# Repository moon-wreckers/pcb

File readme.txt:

Team I - MRSD'18
				Power Distribution Board
					   6 Nov 2017

Summary:
	
	The necessary features for the power distribtion board are to power the camera (12V, 0.42A), motor drivers 2x(12V, 15-20A), steering motors 2x(12V, 0.42A), the HTC VIVE beacon (12V, 0.40A), winch mechanism(5V, 0.90A), on-board computer(5V, 3A), GPS(5V, 0.08A) and inertial measurement unit (5V, 0.05A).
	
Maximum 12v Current: 42.06A
Maximum Theoretical Current: 45.19A
Total Nominal Current: 4.09A

Discussion:
	The on-board power supply is from a set of 12V batteries. Considering that majority of the on-board components have to powered using 12V supply - we have designed a 12V power distribution board, that further reduces to 5V wherever necessary. In order to have a bank of the 5V power supply pins, we have an off the shelf 12V-5V power regulator, that has been supplied with the on-board computer, as the power source to the extendable 5V power bank. 

	Further, in order to limit the power (current) drawn by various components the supply has been branched to shield components that have current limit less than or equal to 3A, 6.25A and 25A (15 + 6.25 +3 A).
	
	For example, the 12V to 5V regulator will be powered by the [12V, 3A] branch. Thus, protecting the components from (sudden, uncpredicted) excessive power requirements owing to unknown external conditions.

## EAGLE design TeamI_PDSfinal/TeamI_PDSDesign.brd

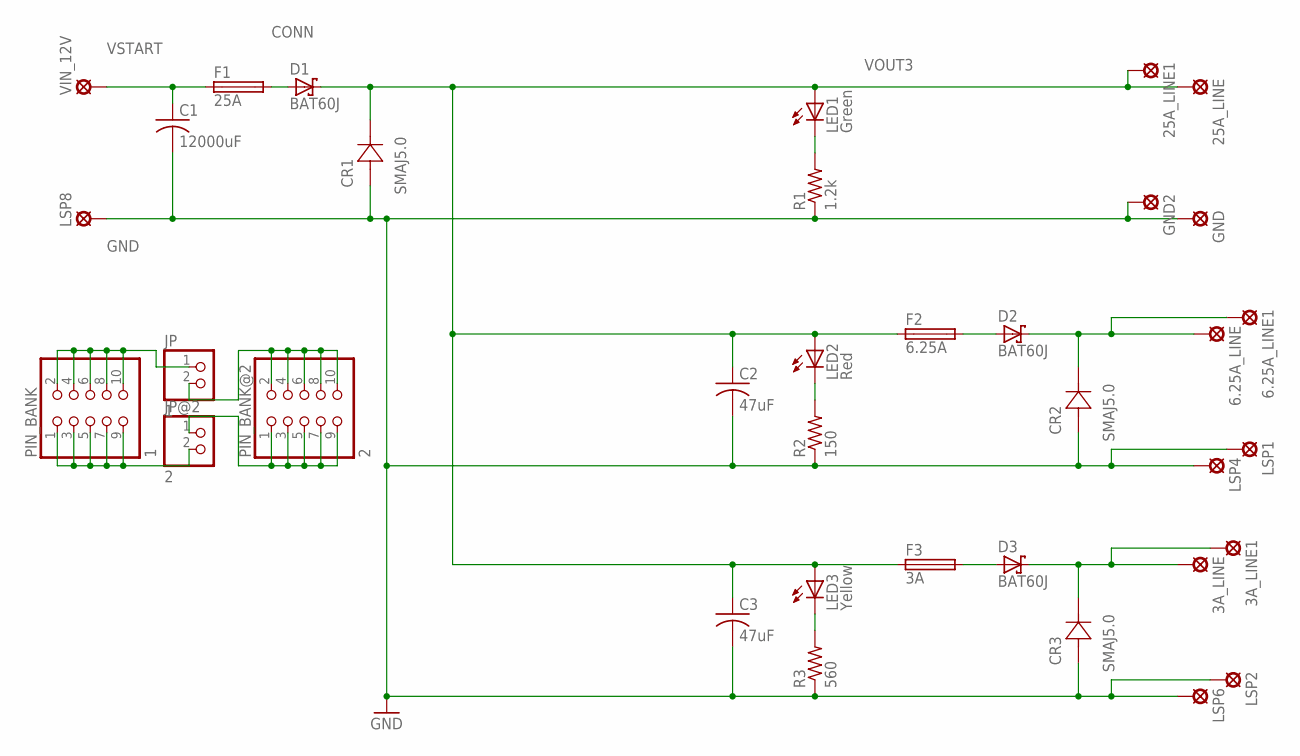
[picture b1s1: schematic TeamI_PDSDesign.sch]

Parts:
3A_LINE, 3A_LINE1, 6.25A_LINE, 6.25A_LINE1, 25A_LINE, 25A_LINE1: SE13
C1: 12000uF; C1206K
C2, C3: 47uF; C1206K
CR1, CR2, CR3: SMAJ5.0; SMASERIES
D1, D2, D3: BAT60J; SOD323_ST
F1: 25A; TE5
F2: 6.25A; TE5
F3: 3A; TE5
GND, GND2: SE13
JP: 1; 1X02
JP@2: 2; 1X02
LED1: Green; CHIPLED_1206
LED2: Red; CHIPLED_1206
LED3: Yellow; CHIPLED_1206
LSP1, LSP2, LSP4, LSP6, LSP8: SE13
PIN_BANK: 1; 2X05
PIN_BANK@2: 2; 2X05
R1: 1.2k; R1206
R2: 150; R1206
R3: 560; R1206
VIN_12V: SE13

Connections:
CONN: D1.A, F1.2
GND: C1.2, C2.2, C3.2, CR1.2 (1), CR2.2 (1), CR3.2 (1), GND.MP, GND2.MP, LSP1.MP, LSP2.MP, LSP4.MP, LSP6.MP, LSP8.MP, R1.1, R2.1, R3.1
unnamed: JP@2.1, PIN_BANK@2.1, PIN_BANK@2.3, PIN_BANK@2.5, PIN_BANK@2.7, PIN_BANK@2.9
unnamed: JP@2.2, PIN_BANK.1, PIN_BANK.3, PIN_BANK.5, PIN_BANK.7, PIN_BANK.9
unnamed: LED1.C, R1.2
unnamed: JP.1, PIN_BANK.2, PIN_BANK.4, PIN_BANK.6, PIN_BANK.8, PIN_BANK.10
unnamed: JP.2, PIN_BANK@2.2, PIN_BANK@2.4, PIN_BANK@2.6, PIN_BANK@2.8, PIN_BANK@2.10
unnamed: D2.A, F2.2
unnamed: 6.25A_LINE.MP, 6.25A_LINE1.MP, CR2.1 (2), D2.C
unnamed: LED2.C, R2.2
unnamed: D3.A, F3.2
unnamed: 3A_LINE.MP, 3A_LINE1.MP, CR3.1 (2), D3.C
unnamed: LED3.C, R3.2
VOUT3: 25A_LINE.MP, 25A_LINE1.MP, C2.1, C3.1, CR1.1 (2), D1.C, F2.1, F3.1, LED1.A, LED2.A, LED3.A
VSTART: C1.1, F1.1, VIN_12V.MP

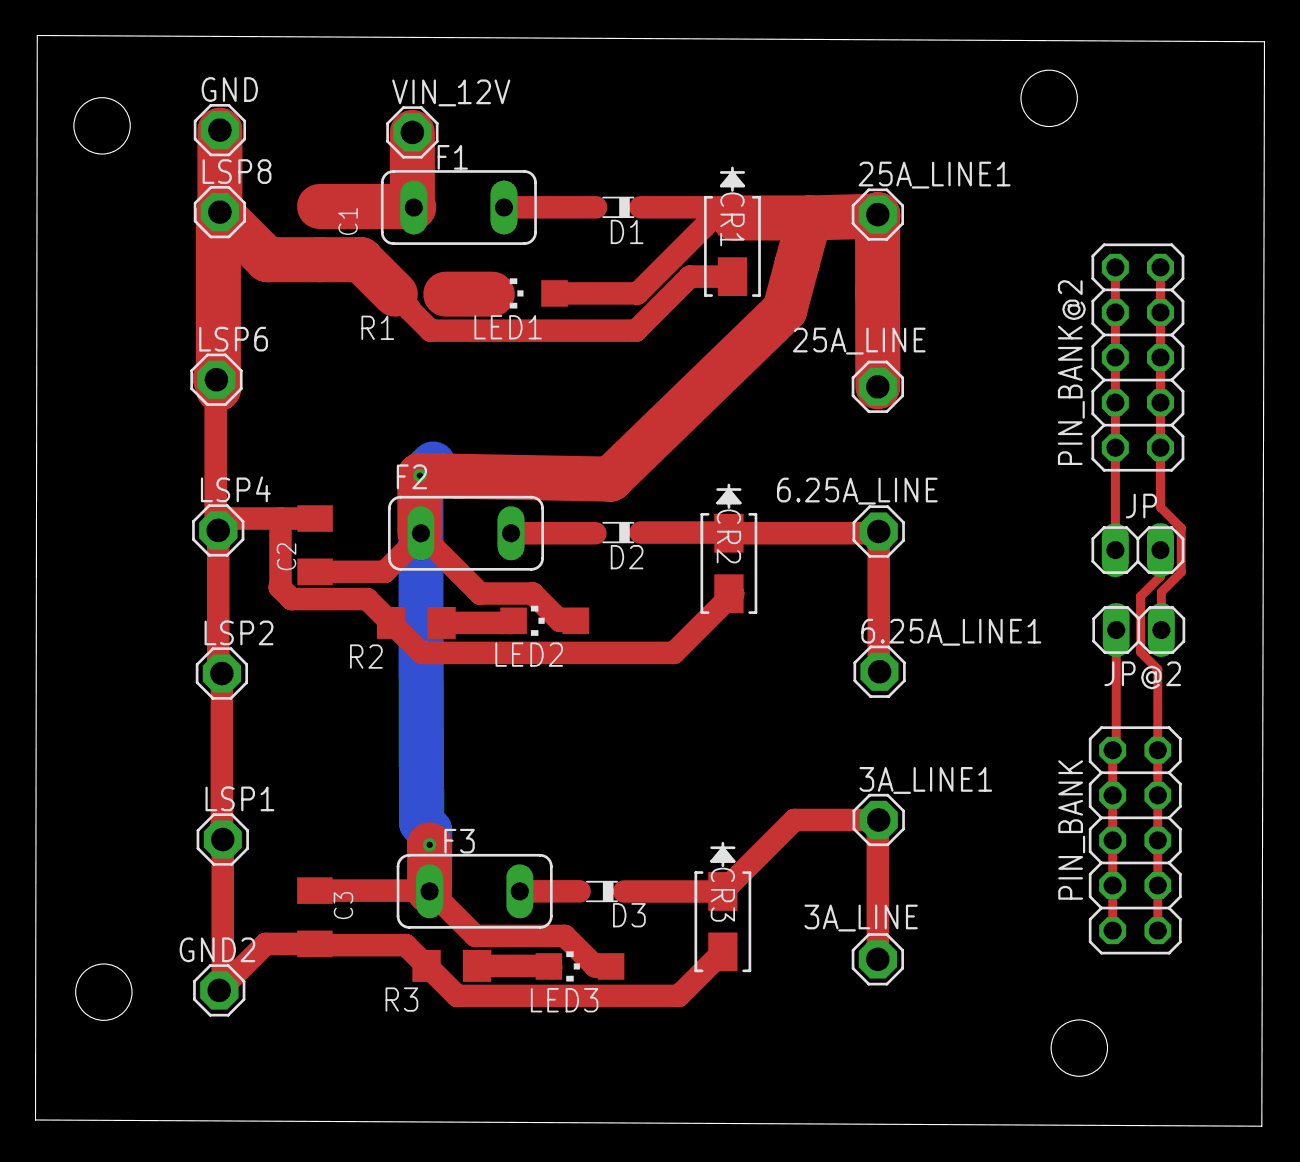
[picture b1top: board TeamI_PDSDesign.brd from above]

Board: 2 copper layers, 69.2 x 61.4 mm, 36 parts (0 on the bottom side), 15 nets.

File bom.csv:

"Part";"Value";"Device";"Package";"Description";"MANUFACTURER_PART_NUMBER";"MF";"MPN";"OC_FARNELL";"OC_NEWARK";"VENDOR";
"3A_LINE";"SE13";"SE13";"SE13";"SOLDER PAD E1542,  drill 1,3mm, distributor Buerklin, 07F815";"";"";"";"";"";"";
"3A_LINE1";"SE13";"SE13";"SE13";"SOLDER PAD E1542,  drill 1,3mm, distributor Buerklin, 07F815";"";"";"";"";"";"";
"6.25A_LINE";"SE13";"SE13";"SE13";"SOLDER PAD E1542,  drill 1,3mm, distributor Buerklin, 07F815";"";"";"";"";"";"";
"6.25A_LINE1";"SE13";"SE13";"SE13";"SOLDER PAD E1542,  drill 1,3mm, distributor Buerklin, 07F815";"";"";"";"";"";"";
"25A_LINE";"SE13";"SE13";"SE13";"SOLDER PAD E1542,  drill 1,3mm, distributor Buerklin, 07F815";"";"";"";"";"";"";
"25A_LINE1";"SE13";"SE13";"SE13";"SOLDER PAD E1542,  drill 1,3mm, distributor Buerklin, 07F815";"";"";"";"";"";"";
"C1";"12000uF";"C-USC1206K";"C1206K";"CAPACITOR, American symbol";"";"";"";"";"";"";
"C2";"47uF";"C-USC1206K";"C1206K";"CAPACITOR, American symbol";"";"";"";"";"";"";
"C3";"47uF";"C-USC1206K";"C1206K";"CAPACITOR, American symbol";"";"";"";"";"";"";
"CR1";"SMAJ5.0";"SMAJ5.0";"SMASERIES";"";"SMAJ5.0";"";"";"";"";"Littelfuse Inc";
"CR2";"SMAJ5.0";"SMAJ5.0";"SMASERIES";"";"SMAJ5.0";"";"";"";"";"Littelfuse Inc";
"CR3";"SMAJ5.0";"SMAJ5.0";"SMASERIES";"";"SMAJ5.0";"";"";"";"";"Littelfuse Inc";
"D1";"BAT60J";"BAT60J";"SOD323_ST";"Schottky barrier diode";"";"";"";"";"";"";
"D2";"BAT60J";"BAT60J";"SOD323_ST";"Schottky barrier diode";"";"";"";"";"";"";
"D3";"BAT60J";"BAT60J";"SOD323_ST";"Schottky barrier diode";"";"";"";"";"";"";
"F1";"25A";"TE5";"TE5";"FUSE";"";"";"";"unknown";"unknown";"";
"F2";"6.25A";"TE5";"TE5";"FUSE";"";"";"";"unknown";"unknown";"";
"F3";"3A";"TE5";"TE5";"FUSE";"";"";"";"unknown";"unknown";"";
"GND";"SE13";"SE13";"SE13";"SOLDER PAD E1542,  drill 1,3mm, distributor Buerklin, 07F815";"";"";"";"";"";"";
"GND2";"SE13";"SE13";"SE13";"SOLDER PAD E1542,  drill 1,3mm, distributor Buerklin, 07F815";"";"";"";"";"";"";
"JP";"1";"PINHD-1X2";"1X02";"PIN HEADER";"";"";"";"";"";"";
"JP@2";"2";"PINHD-1X2";"1X02";"PIN HEADER";"";"";"";"";"";"";
"LED1";"Green";"LEDCHIPLED_1206";"CHIPLED_1206";"LED";"";"";"";"";"";"";
"LED2";"Red";"LEDCHIPLED_1206";"CHIPLED_1206";"LED";"";"";"";"";"";"";
"LED3";"Yellow";"LEDCHIPLED_1206";"CHIPLED_1206";"LED";"";"";"";"";"";"";
"LSP1";"SE13";"SE13";"SE13";"SOLDER PAD E1542,  drill 1,3mm, distributor Buerklin, 07F815";"";"";"";"";"";"";
"LSP2";"SE13";"SE13";"SE13";"SOLDER PAD E1542,  drill 1,3mm, distributor Buerklin, 07F815";"";"";"";"";"";"";
"LSP4";"SE13";"SE13";"SE13";"SOLDER PAD E1542,  drill 1,3mm, distributor Buerklin, 07F815";"";"";"";"";"";"";
"LSP6";"SE13";"SE13";"SE13";"SOLDER PAD E1542,  drill 1,3mm, distributor Buerklin, 07F815";"";"";"";"";"";"";
"LSP8";"SE13";"SE13";"SE13";"SOLDER PAD E1542,  drill 1,3mm, distributor Buerklin, 07F815";"";"";"";"";"";"";
"PIN_BANK";"1";"PINHD-2X5";"2X05";"PIN HEADER";"";"";"";"";"";"";
"PIN_BANK@2";"2";"PINHD-2X5";"2X05";"PIN HEADER";"";"";"";"";"";"";
"R1";"1.2k";"R-US_R1206";"R1206";"RESISTOR, American symbol";"";"";"";"";"";"";
"R2";"150";"R-US_R1206";"R1206";"RESISTOR, American symbol";"";"";"";"";"";"";
"R3";"560";"R-US_R1206";"R1206";"RESISTOR, American symbol";"";"";"";"";"";"";
"VIN_12V";"SE13";"SE13";"SE13";"SOLDER PAD E1542,  drill 1,3mm, distributor Buerklin, 07F815";"";"";"";"";"";"";

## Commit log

2017-10-05 added eagle libraries
2017-10-05 initial writeup
2017-10-05 vaguely rearranged board layout
2017-10-06 update the schematic and layout
2017-10-06 update write up
2017-10-06 Rename Eagle\Eagle\Eagle.sch to voltage_regulator.sch
2017-10-10 fixed stupid filenames
2017-10-25 adding 12_5V_5A regulator
2017-10-25 initial commit for swtiching the voltage regulators
2017-10-25 removed 3.3V regulation, corrected name tags, switched 5V regulator, removed terminal connectors (DAN will make surface mount pad in the layout)
2017-10-25 changed stupid font size stupidly because eagle is stupid
2017-11-02 found a DCDC converter
2017-11-03 schematic with different current rating for 12V power supply
2017-11-03 finished board layout
2017-11-07 adding extenders for each 12V section
2017-11-07 ERC check complete
2017-11-07 finished.
2017-11-07 adding the conceptual design document
2017-11-07 moving BOM to git repo
2017-11-07 Gerber and BoM added.
2017-11-07 With Submission folder and Zip
